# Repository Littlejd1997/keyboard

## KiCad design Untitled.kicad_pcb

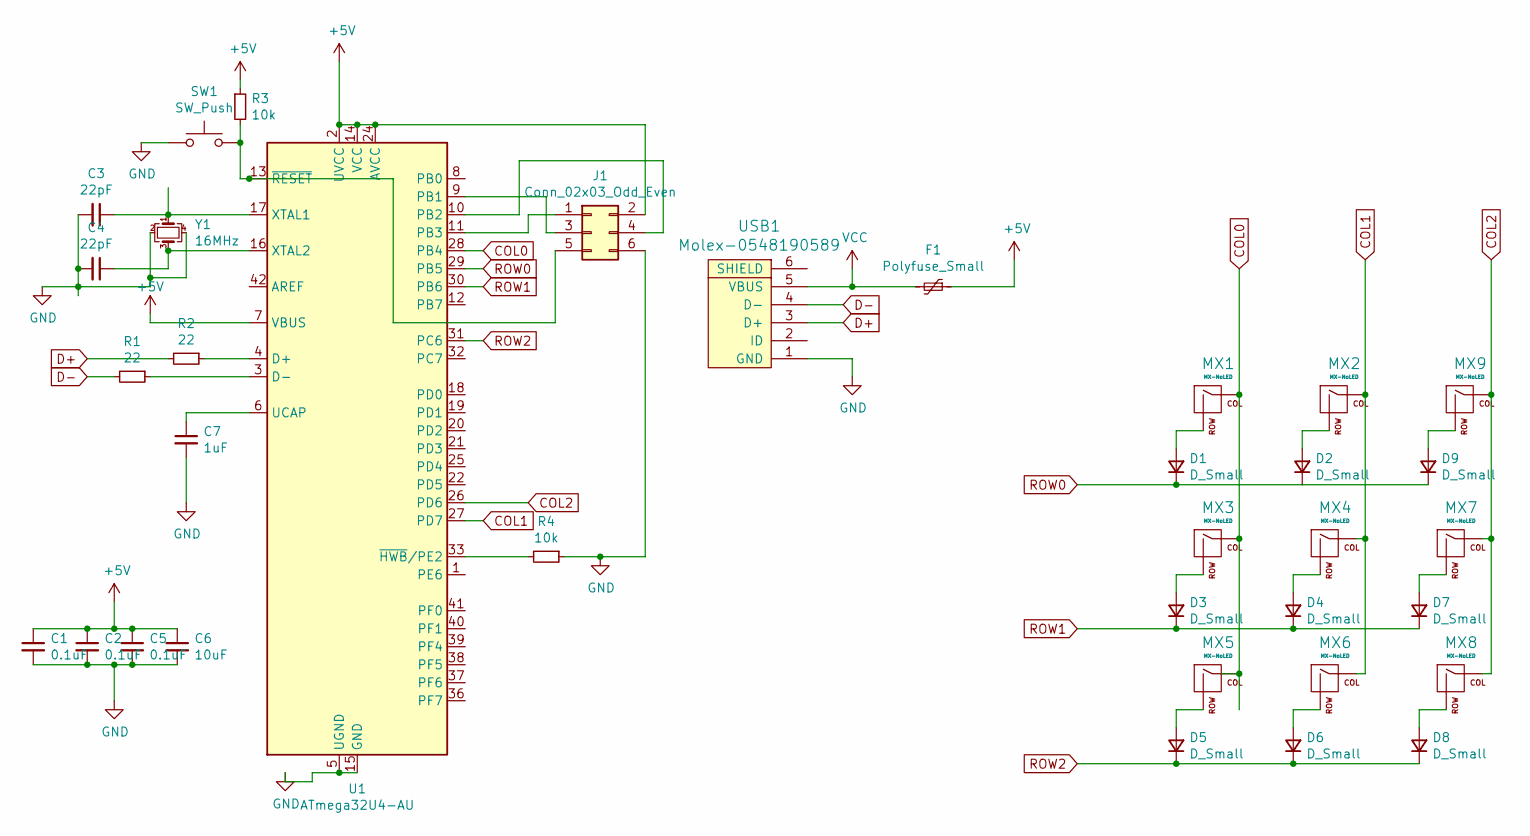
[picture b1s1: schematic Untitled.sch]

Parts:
C1, C2, C5: 0.1uF; C_0805_2012Metric
C3, C4: 22pF; C_0805_2012Metric
C6: 10uF; C_0805_2012Metric
C7: 1uF; C_0805_2012Metric
D1, D2, D3, D4, D5, D6, D7, D8, D9: D_Small; D_SOD-123
F1: Polyfuse_Small; Fuse_1206_3216Metric
J1: Conn_02x03_Odd_Even; PinHeader_2x03_P2.54mm_Vertical
MX1, MX2, MX3, MX4, MX5, MX6, MX7, MX8, MX9: MX-NoLED; MX-1.5U-NoLED
R1, R2: 22; R_0805_2012Metric
R3, R4: 10k; R_0805_2012Metric
SW1: SW_Push; SKQG-1155865
U1: ATmega32U4-AU; TQFP-44_10x10mm_P0.8mm
USB1: Molex-0548190589
Y1: 16MHz; Crystal_SMD_3225-4Pin_3.2x2.5mm

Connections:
+5V: C1.1, C2.1, C5.1, C6.1, F1.1, J1.2, R3.1, U1.2 (UVCC), U1.7 (VBUS), U1.14 (VCC), U1.24 (AVCC), U1.34 (VCC), U1.44 (AVCC)
COL0: MX1.1 (COL), MX3.1 (COL), MX5.1 (COL), U1.28 (PB4)
COL1: MX2.1 (COL), MX4.1 (COL), MX6.1 (COL), U1.27 (PD7)
COL2: MX7.1 (COL), MX8.1 (COL), MX9.1 (COL), U1.26 (PD6)
D+: R2.2, USB1.3 (D+)
D-: R1.2, USB1.4 (D-)
GND: C1.2, C2.2, C3.2, C4.2, C5.2, C6.2, C7.2, J1.6, R4.1, SW1.1, U1.5 (UGND), U1.15 (GND), U1.23 (GND), U1.35 (GND), U1.43 (GND), USB1.1 (GND), Y1.2, Y1.4
unnamed: C3.1, U1.17 (XTAL1), Y1.1
unnamed: C4.1, U1.16 (XTAL2), Y1.3
unnamed: C7.1, U1.6 (UCAP)
unnamed: D1.2 (A), MX1.2 (ROW)
unnamed: D2.2 (A), MX2.2 (ROW)
unnamed: D3.2 (A), MX3.2 (ROW)
unnamed: D4.2 (A), MX4.2 (ROW)
unnamed: D5.2 (A), MX5.2 (ROW)
unnamed: D6.2 (A), MX6.2 (ROW)
unnamed: D7.2 (A), MX7.2 (ROW)
unnamed: D8.2 (A), MX8.2 (ROW)
unnamed: D9.2 (A), MX9.2 (ROW)
unnamed: J1.1, U1.11 (PB3)
unnamed: J1.3, U1.9 (PB1)
unnamed: J1.4, U1.10 (PB2)
unnamed: J1.5, R3.2, SW1.2, U1.13 (~RESET)
unnamed: R1.1, U1.3 (D-)
unnamed: R2.1, U1.4 (D+)
unnamed: R4.2, U1.33 (~HWB~/PE2)
ROW0: D1.1 (K), D2.1 (K), D9.1 (K), U1.29 (PB5)
ROW1: D3.1 (K), D4.1 (K), D7.1 (K), U1.30 (PB6)
ROW2: D5.1 (K), D6.1 (K), D8.1 (K), U1.31 (PC6)
VCC: F1.2, USB1.5 (VBUS)

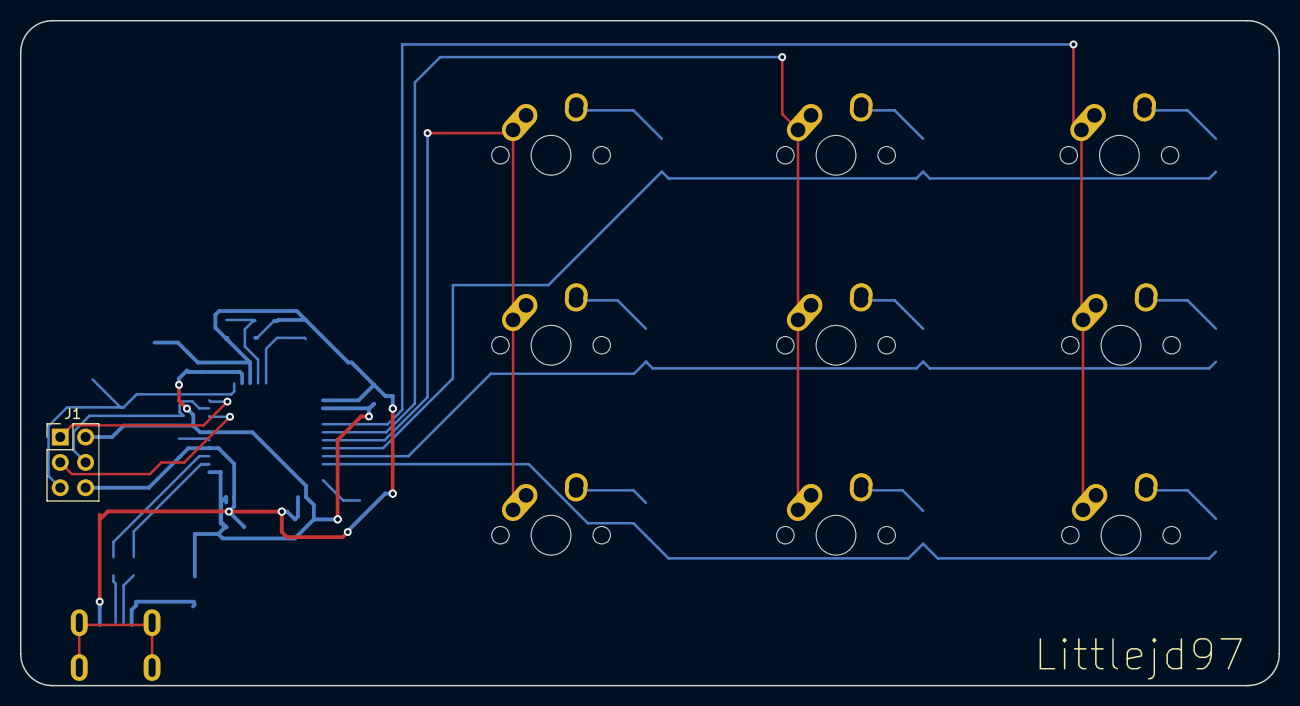
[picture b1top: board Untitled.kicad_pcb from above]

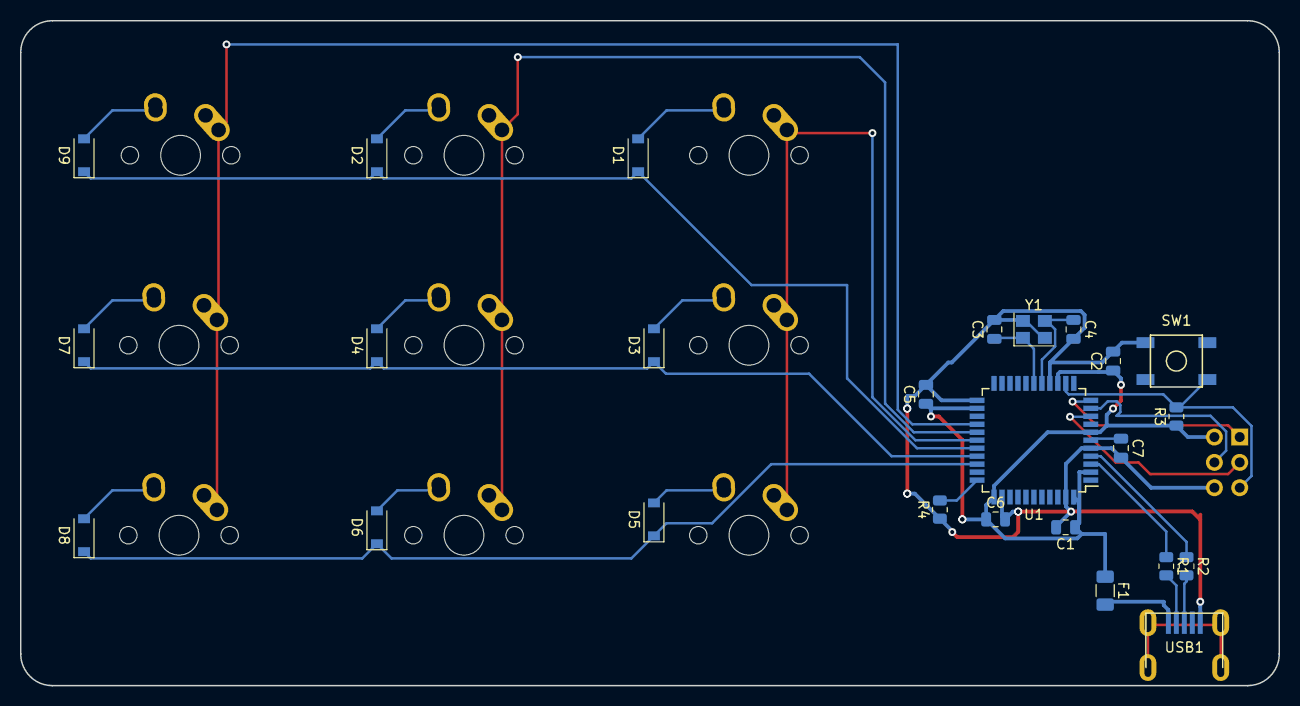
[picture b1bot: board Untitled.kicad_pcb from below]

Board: 2 copper layers, 126.2 x 66.7 mm, 35 parts (25 on the bottom side), 30 nets.

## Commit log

2021-06-13 Add submodules
2021-06-13 Add libraries
2021-06-13 rest of the electrical
2021-06-15 Routed MCU
2021-08-14 Keyboard - ICSP - Fixed USB D+/D-
